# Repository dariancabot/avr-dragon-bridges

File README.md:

avr-dragon-bridges
==================

AVR Dragon easy pin bridges

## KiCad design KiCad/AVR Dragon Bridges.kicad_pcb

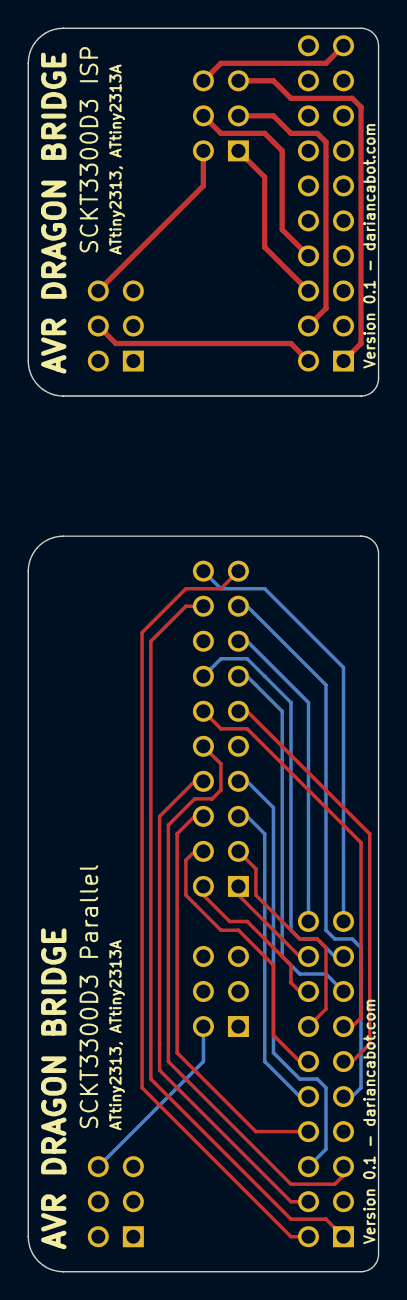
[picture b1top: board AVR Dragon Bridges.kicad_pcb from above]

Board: 2 copper layers, 25.4 x 90.2 mm, 7 parts (0 on the bottom side), 26 nets.

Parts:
P6, P11: ISP_HEADER_IL; pin_array_3x2
P9, P14: VCC_HEADER_IL; pin_array_3x2
P10, P15: EXPAND_HEADER_IL; MCU_10X2
P13: HV_PROG_HEADER_IL; pin_array_10x2

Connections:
unnamed: P6.6, P10.10
unnamed: P6.5, P10.1
unnamed: P6.2, P9.6
unnamed: P6.4, P10.17
unnamed: P6.3, P10.19
unnamed: P6.1, P10.18
unnamed: P9.4, P10.20
unnamed: P13.13, P15.8
unnamed: P13.12, P15.7
unnamed: P13.15, P15.11
unnamed: P13.14, P15.9
unnamed: P13.11, P15.6
unnamed: P13.10, P15.3
unnamed: P13.8, P15.19
unnamed: P13.18, P15.1
unnamed: P13.20, P15.10
unnamed: P13.19, P15.20
unnamed: P13.17, P15.5
unnamed: P13.4, P15.15
unnamed: P13.7, P15.18
unnamed: P13.6, P15.17
unnamed: P13.5, P15.16
unnamed: P13.3, P15.14
unnamed: P13.2, P15.13
unnamed: P13.1, P15.12
unnamed: P11.2, P14.6

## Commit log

2014-04-28 Set up KiCad project and component library for AVR Dragon headers. Added preliminary schematic for Devicesheet SCKT3300D3 (ATtiny2313).
2014-04-28 Completed preliminary PCB for ATtiny2313. Tidied up some schematics.
